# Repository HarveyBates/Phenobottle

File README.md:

---

### Description

An open-source Raspberry-Pi based photobioreactor for cultivating and assessing physiology (photosynthesis & productivity) in microscopic algae. The device can be used to cultivate both green algae and cyanobacteria while continuiously (and non-invasively) probing photosynthetic and growth phenotypes.

#### Publication

The device was published in [Algal Research in 2020](https://www.sciencedirect.com/science/article/abs/pii/S2211926420309735):

*The Phenobottle, an open-source photobioreactor platform for environmental simulation - Bates et al. 2020*

#### Future of The Phenobottle

The Phenobottle is currently being updated to version 0.2. This will feature several environmental controls that were not featured the original version (v0.1) of the device. Additonal environmental sensors will also feature in version 0.2 along with a graphical user interface (GUI). 

If you would like to learn more about the progress of this version please email: [harvey_bates@hotmail.com](harvey_bates@hotmail.com)

---

### [Live](https://youtu.be/7FyAfFrLizw) Preview

___

# Operating Manual

## Specifications

| Feature                                                      | Value / Description                                          |
| ------------------------------------------------------------ | ------------------------------------------------------------ |
| Growth light quality                                         | Red, green and blue (Adjustable). 8-bit individual adjustment for each channel. |
| Growth light intensity                                       | Up to 200 &mu;E (can be increased if needed).                |
| Mixing                                                       | Vertical mixing using magnetic stirrer (adjustable intensity) |
| Bubbling                                                     | Included bubbling motor (adjustable) or solenoid control for external supply of CO<sub>2</sub> |
| Main board                                                   | Raspberry Pi 3B+ (can accomidate the new 4 - 4B)             |
| Microcontroller                                              | Teensy 3.5/3.6 or Teensy 4.1 (3.6 Recommended)               |
| Actinic LED colors                                           | **Blue** 455 – 485 nm (466 nm), **Green** 517 – 555 nm (532 nm), **Orange** 583 – 600 nm (593 nm), **Red** 617 – 635 nm (626 nm). |
| Resolution of **optical density** and **chlorophyll fluorescence** measurments | 10 to 16-bit (adjustable)                                    |
| Sampling rate of fluorometer                                 | 8 &mu;s at 12-bits (can be overclocked)                      |
| Operating voltage                                            | 15 V 1.2 A (Barrel plug), 12 V 2 A (Barrel Plug) and a 5 V 2 A (MicroUSB) power supply |
| Data collection                                              | SQL Server and local .csv                                    |

## Downloading files from this repository

As the Phenobottle is being updated constantly, please download a released version of the device from the releases tab (located on the right hand side of the screen). This contains all the files needed to 3D-print and control Phenobottles as well as some information about the required materials and tools. 

If you wish to clone the main repository you may; however, as there are new versions of the Phenobottle in the works, the files may not work as planned.

## Python dependencies

A number of packages are included in the [Phenobottle_RaspberryPi.py](Phenobottle_RaspberryPi.py). Some of which are already installed on a Raspberry Pi and as such wont be discussed. Others need to be installed using the Raspberry Pi terminal before compiling, these include: 
### PyMySQL - For SQL connection
#### Terminal
```bash
pip3 install PyMySQL
```
#### Python
```python
import pymysql.cursors
```
This requires a Raspberry Pi to be configured as a dedicated SQL server. Information on how to do that can be found [here](https://pimylifeup.com/raspberry-pi-mysql/). It is recomended that you use a dedicated Raspberry Pi for the SQL server; however, you can use one of the Phenobottle's Raspberry Pi's as a server if you are limited.

### Adafruit_MotorHAT - For I2C communication with the [Adafruit-MotorHAT](https://www.adafruit.com/product/2348)
#### Terminal
```bash
git clone https://github.com/adafruit/Adafruit-Motor-HAT-Python-Library.git
cd Adafruit-Motor-HAT-Python-Library
python3 setup.py install
```
#### Python
```python
from Adafruit_MotorHAT import Adafruit_MotorHAT
```
Unfortunatly this package is depreciated; however, its still fine to use for the Phenobottle.

### Twilio - SMS messaging
#### Terminal
```bash
pip3 install twilio
```
#### Python
```python
from twilio.rest import Client
```
This package is not required if you do not want to recieve SMS updates. Twilio is a paid service that you must sign up for [here](https://www.twilio.com/). However, this is non-essential and the Phenobottle runs fine without this addition. This can be handy if you are away from The Phenobottle and need to know how the experiment is running. 

### pySerial - Serial (USB) communication with the microcontroller
#### Terminal
```bash
python3 -m pip install pyserial
```
#### Python
```python
import serial
```
Required for communication with the Teensy 3.6 microcontroller. Documentation on this package can be found [here](https://pyserial.readthedocs.io/en/latest/index.html). 

## Required setup in [Phenobottle_RaspberryPi.py](Phenobottle_RaspberryPi.py)
### Basic Setup
```python
PHENOBOTTLE_NUMBER = 3 # Arbitary number to differentiate between Phenobottles
INITIAL_OPTICAL_DENSITY = 888 # 12-bit value obtained by calibrating the optical density sensor
ARDUINO_FLUORESCENCE_REFERENCE = 3.3 # Teensy microntrollers have 2 analog reference values 1.1 and 3.3 
MIXING_SPEED = 32 # Mixing speed of the mixing motor (0 - 255)
BUBBLING_INTENSITY = 60 # Bubbling intensity of the bubbling motor (0 - 255)
LIGHT_INTENSITY = 220 # Overall light intensity of the grow lights (0 - 255) 
PERISTALTIC_SPEED = 160 # Speed of the peristaltic pump (0 - 255)
EXPERIMENT_START_TIME = "07:00:00" # Specify when the experiment should start 

ser = serial.Serial('/dev/ttyACM0', 115200) # Serial port and baud rate of Teensy 3.6 microcontroller
```
The `INITAL_OPTICAL_DENSITY` value is obtained by reading the raw value of optical density BEFORE adding microalgae to the flask. This can be acheived by writing "MeasureOpticalDensity" in the serial input of the Teensy 3.6 microcontroller (in the ArduinoIDE) or calling `Test.prelim_od()` in the python [file](Phenobottle_RaspberryPi.py). This is required to obtain a 100% transmission reading for which optical density measurments can be formulated from in the code. 

### SQL Setup
```python
connection = pymysql.connect(host='IP_ADDRESS', # IP address of Raspberry Pi SQL server
                             port=port_number, # Usually 3306
                             user='Username', # Username of phpmyadmin 
                             password='Password', # Password of phpmyadmin
                             db='Phenobottle No.%s' %PHENOBOTTLE_NUMBER, # Database name
                             charset='utf8mb4',
                             cursorclass=pymysql.cursors.DictCursor)
```
For a SQL server connection this command must be compiled. See [here](https://pypi.org/project/PyMySQL/) for some documentation related to PyMySQL. For the database name you can change this to whichever name you choose; however, here we have premaded databases in out SQL server named "Phenobottle No.1", "Phenobottle No.2" ..., so that the `PHENOBOTTLE_NUMBER` corresponds with the correct database. 

### Messaging Setup
```python
acc_sid = "Account SSID" # Accound SSID from Twilio
auth_token = "Account Token" # Accound token from Twilio
client = Client(acc_sid, auth_token)
from_number = "Twilio Phone Number" # Designated twilio phone number
to_number = "Mobile Phone Number" # Your phone number
```
As mentioned above, this part isn't really nessessary. However, information regarding the setup of SMS messaging can be found [here](https://www.twilio.com/).

## Experimental procedure
### Measurment Intervals
The Phenobottle is capable of measuring/controling environmental variables at described intervals. This is done through this set of commands:
```python
""" Here we can check if the current time in minutes is devisable by our required measuring interval in this case 10 minutes. This means every 10 minutes a routine (day or night) will be run."""
if datetime.datetime.now().minute % 10 == 0: 
    """ Here we can setup or morning (8:00) and night times (20:00)"""
    if Experiment.experiment_schedule(datetime.time(8, 00), datetime.time(20, 00)): 
        NOW = datetime.datetime.now()
        Experiment.day_routine() # Runs the day routine
    else:
        NOW = datetime.datetime.now() 
        Experiment.night_routine() # Runs the night routine
```
### Routines
The day and the night routine are idential except for the fact that during the night the LED grow lights are constantly switched OFF. 
```python
MotorsAndLights.light_on(None) # Turn on lights (daytime only) with desired color
MotorsAndLights.mixing_motor_on() # Mixing on at set speed
time.sleep(30) # Wait 30 seconds for mixing 

MotorsAndLights.mixing_motor_off() # Mixing off
MotorsAndLights.light_off() # Lights off to ensure no noise from PWM interferes with measurments
Sensors.measure_optical_density() # Measures optical density
Sensors.measure_fluorescence() # Measures fluorescence

MotorsAndLights.light_on(None) # Turn on lights (daytime only) with desired color
MotorsAndLights.peristaltic_motor_on() # Pump on to clear cuvette
Database.upload() # Upload to SQL server
Excel.upload() # Upload to local .csv file
time.sleep(20) # Wait for pump to clear cuvette 

MotorsAndLights.peristaltic_motor_off() # Stop pump
MotorsAndLights.bubbling_motor_on() # Bubble main culture flask on
MotorsAndLights.mixing_motor_on() # Mixing on to homogenate culture
time.sleep(30) # Wait 30 seconds for bubbling and mixing 

MotorsAndLights.bubbling_motor_off() # Bubbling off
MotorsAndLights.mixing_motor_off() # Mixing off
```
This procedure is completely customisable, i.e. methods can be swapped around and the length of certain processes such as the bubbling time can be increased easily. 

# [Teensy 3.6](https://www.pjrc.com/store/teensy36.html) Microcontroller 
Analog functions are carried out by a Teensy 3.6 microcontroller which is connected to the Rasberry Pi via a serial (USB) connection. These analog functions include the measurement of optical density (growth), temperture and chlorophyll fluorescence (photosynthesis). 

The Teensy microcontroller can be programed with the [Arduino IDE](https://www.arduino.cc/en/Main/Software) on the Raspberry Pi if the additional software provided by [PJRC](https://www.pjrc.com/) called [Teensyduino](https://www.pjrc.com/teensy/teensyduino.html) is installed. 

The Teensy [code](Phenobottle_Teensy.ino) is flashed to the Teensy board and doesn't need modifying as it acts as a slave to the Raspberry Pi. 

## Teensy Setup
```c++
void setup() {
  Serial.begin(115200); // Initalise serial communications at specific baud rate
  analogReadResolution(12); // Set the resolution of the microcontroller in bits
  set_reference_voltage(refVoltage); // Only applicable with a Teensy 3.6 (disable if using other microcontroller)
  ...
}
```
## Teensy Slave Setup
The Teensy is constantly checking if there is requests in its serial port from the Raspberry Pi. It does this via the main loop:
```c++
void loop(){
  if(Serial.available()){   
    command = Serial.readStringUntil('\n');
    if(command.equals("MeasureOpticalDensity") || command.equals("MOD")){
      measure_optical_density();
    }
    else if(command.equals("MeasureFluorescence") || command.equals("MF")){
      measure_fluorescence();
    }
    ...
}
```
For example, when a string containing ```"MeasureOpticalDensity"``` into the Teensy's serial port, the resulting function ```measure_optical_density()``` is carried out. This simple design makes it easy to add new requests from the Raspberry Pi [.py](Phenobottle_RaspberryPi.py) file and the Teensy [.ino](Phenobottle_Teensy.ino) file by adding a new `else if` statement to this loop. 

## Fluorescence Measurment
### Setup
The Teensy in its current configuration takes a one second measurement of chlorophyll fluorescence, this however, can be adjusted as described below. The first part is to create arrays of different sizes corresponding to the time between measurements of fluorescence. The one second measurement is comprised of over 2000 data points which are comprised of fast (microsecond timescales) and slow (millisecond timescales) measurments:
2. Micro - Comprised of microsecond measurments (~8 &mu;s between measurments) of a set amount
3. Milli - Comprised of millisecond measurements (~1 ms between measurements) of a set amount
```c++
// Setup arrays that hold fluorescence data
int microRead [1000];
int milliRead[1000];

// Setup arrays that hold timestamps that correspond to fluorescence values
float microTime[1000]; 
float milliTime[1000];
String command;

int microLength = 1000, milliLength = 1000; // Change these to match the size of the above arrays
```
### Read
The measurment procedure is as follows:
```c++
void measure_fluorescence() {
  set_reference_voltage(refVoltage); 
  digitalWrite(actinicPin, HIGH); // Turn on actinic LED
  long timer = micros(); // Start timer 
  ...
```
The measurment is carried out in two seperate parts (1) `microRead` and (2) `milliRead`. The `analogRead` values are stored in their respective arrays with corresponding timestamps in their own array.
```c++
  // Read microsecond fluorescence values and corresponding timestamps
  for (unsigned int i = 0; i < sizeof(microRead) / sizeof(int); i++) 
  {
    microRead[i] = analogRead(fluorescenceReadPin);
    microTime[i] = micros() - timer;
  }

  // Read millisecond fluorescence values and corresponding timestamps
  for (unsigned int i = 0; i < sizeof(milliRead) / sizeof(int); i++) 
  {
    milliRead[i] = analogRead(fluorescenceReadPin);
    milliTime[i] = micros() - timer;
    delay(1); // Delay ~ 1ms between aqusisitions
  }
  ...
```
Any processing (converting timestamps from `micros` to milliseconds) of the arrays after this measurment is carried out after the actinic LED is switched off. This speeds up the `analogRead` function as we only need to store array values while measuring. 

## Optical Density
Measurment of optical density is really simple. 
```c++
void measure_optical_density(){
  set_reference_voltage(refVoltage);
  digitalWrite(odEmitPin, HIGH); // Turn on emitting LED
  delay(500); // Slight delay to ensure emitting LED is stable
  int odMeasure = analogRead(odReadPin); // Read optical density
  Serial.println(odMeasure);
  digitalWrite(odEmitPin, LOW); // Turn off emitting LED
}
```

# Open-Source Licensing

The software in this work is licensed under GNU AFFERO GENERAL PUBLIC LICENSE
  Copyright (C) (2020)  (Harvey Bates)

  This program is free software: you can redistribute it and/or modify
  it under the terms of the GNU General Public License as published by
  the Free Software Foundation, either version 3 of the License, or
  (at your option) any later version.

  This program is distributed in the hope that it will be useful,
  but WITHOUT ANY WARRANTY; without even the implied warranty of
  MERCHANTABILITY or FITNESS FOR A PARTICULAR PURPOSE.  See the
  GNU General Public License for more details.

  You should have received a copy of the GNU General Public License
  along with this program.  If not, see <https://www.gnu.org/licenses/>

  For more information contact: harvey.bates@student.uts.edu.au

Hardware (3D Models, Electronic Schematics) in this work is licensed under a <a rel="license" href="http://creativecommons.org/licenses/by-sa/3.0/">Creative Commons Attribution-ShareAlike 3.0 Unported License</a>.

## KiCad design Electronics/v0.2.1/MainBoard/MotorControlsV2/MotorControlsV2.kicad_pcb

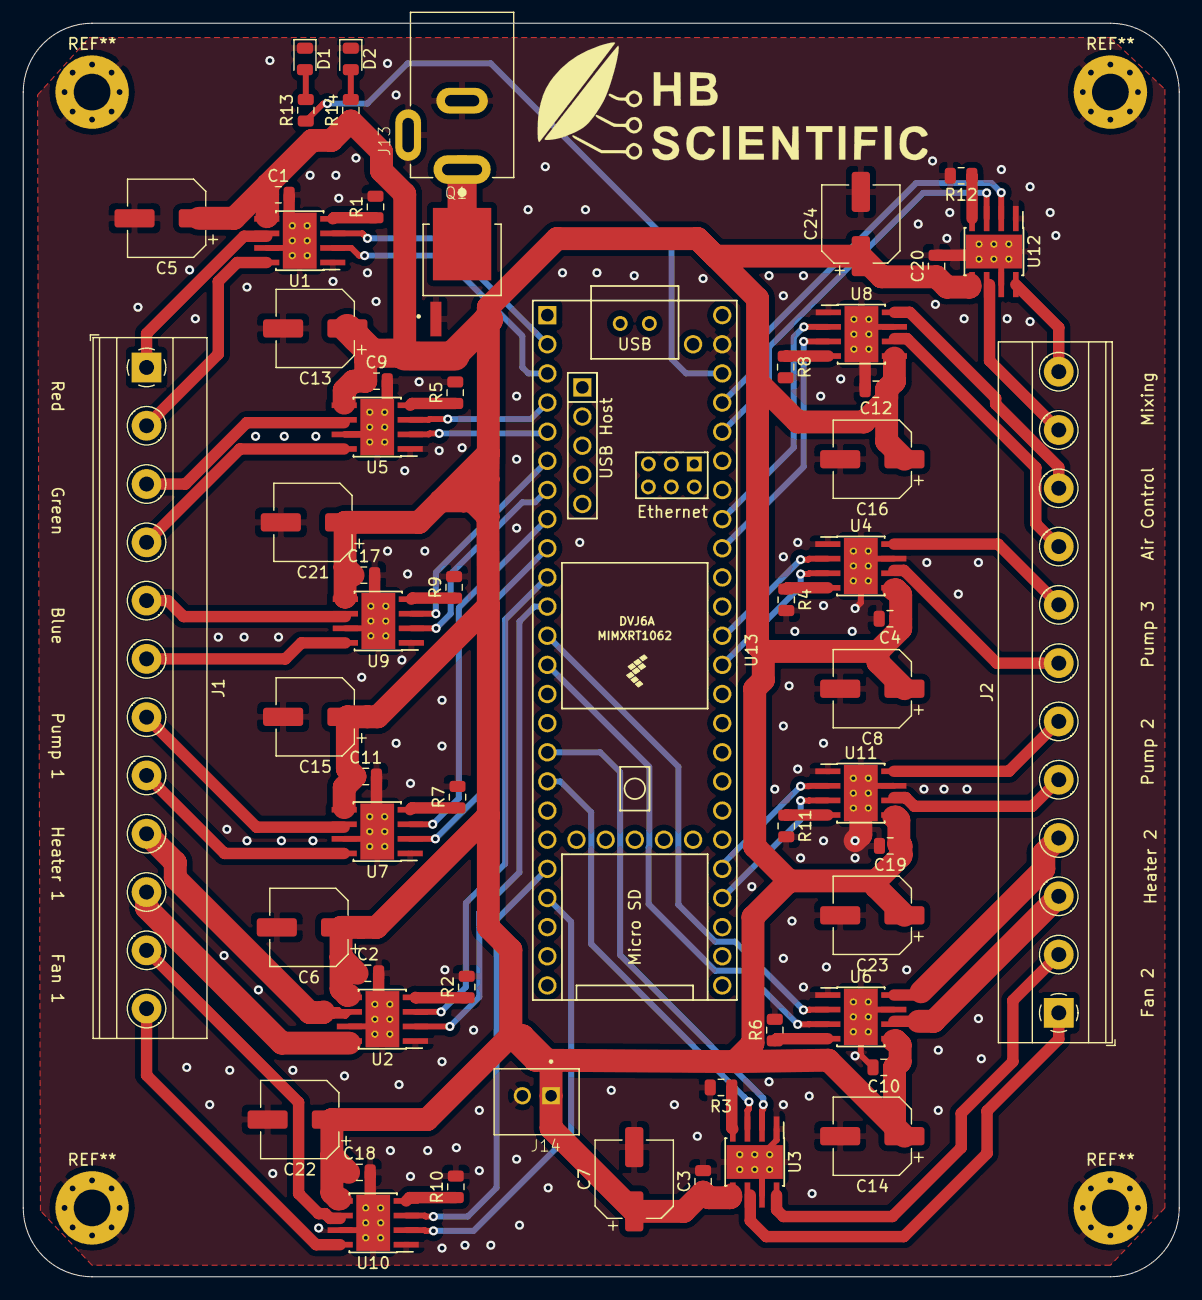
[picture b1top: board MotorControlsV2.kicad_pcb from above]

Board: 2 copper layers, 100.8 x 109.2 mm, 58 parts (0 on the bottom side), 66 nets.

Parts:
C1, C2, C3, C4, C9, C10, C11, C12, C17, C18, C19, C20: 0.1; C_0805_2012Metric
C5, C6, C7, C8, C13, C14, C15, C16, C21, C22, C23, C24: 47uF; CP_Elec_6.3x5.4
D1, D2: LED; LED_0805_2012Metric
J1, J2: Screw_Terminal_01x12; TerminalBlock_Phoenix_MKDS-1,5-12-5.08_1x12_P5.08mm_Horizon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
J13: PJ-002B; CUI_PJ-002B
J14: B2B-XH-A(LF)(SN); JST_B2B-XH-A(LF)(SN)
Q1: AOD417; DPAK228P994X240_3N
R1, R2, R3, R4, R5, R6, R7, R8, R9, R10, R11, R12: 30K; R_0805_2012Metric
R13: 320; R_0805_2012Metric
R14: 5K; R_0805_2012Metric
U1, U2, U3, U4, U5, U6, U7, U8, U9, U10, U11, U12: DRV8871DDA; Texas_HTSOP-8-1EP_3.9x4.9mm_P1.27mm_EP2.95x4.9mm_Mask2.4x3.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
U13: Teensy4.1; Teensy41

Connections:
+3V3: R13.1, U13.46
+12V: C1.1, C2.1, C3.1, C4.1, C5.1, C6.1, C7.1, C8.1, C9.1, C10.1, C11.1, C12.1, C13.1, C14.1, C15.1, C16.1, C17.1, C18.1, C19.1, C20.1, C21.1, C22.1, C23.1, C24.1, J14.1, Q1.3, R14.1, U1.5, U2.5, U3.5, U4.5, U5.5, U6.5, U7.5, U8.5, U9.5, U10.5, U11.5, U12.5
/A1: J2.9, U8.6
/A2: J2.10, U8.8
/B1: J1.5, U9.6
/B2: J1.6, U9.8
/F11: J1.11, U10.6
/F12: J1.12, U10.8
/F21: J2.1, U3.6
/F22: J2.2, U3.8
/G1: J1.3, U5.6
/G2: J1.4, U5.8
/H11: J1.9, U2.6
/H12: J1.10, U2.8
/H21: J2.3, U6.6
/H22: J2.4, U6.8
/M1: J2.11, U12.6
/M2: J2.12, U12.8
/P11: J1.7, U7.6
/P12: J1.8, U7.8
/P21: J2.5, U11.6
/P22: J2.6, U11.8
/P31: J2.7, U4.6
/P32: J2.8, U4.8
/PWM0: U1.3, U13.2
/PWM1: U1.2, U13.3
/PWM2: U5.3, U13.4
/PWM3: U5.2, U13.5
/PWM4: U9.3, U13.6
/PWM5: U9.2, U13.7
/PWM6: U7.3, U13.8
/PWM7: U7.2, U13.9
/PWM8: U2.3, U13.10
/PWM9: U2.2, U13.11
/PWM10: U6.2, U13.12
/PWM11: U6.3, U13.13
/PWM14: U4.3, U13.36
/PWM15: U4.2, U13.37
/PWM18: U8.3, U13.40
/PWM19: U8.2, U13.41
/PWM22: U12.3, U13.44
/PWM23: U12.2, U13.45
/PWM24: U3.2, U13.16
/PWM25: U3.3, U13.17
/PWM28: U10.3, U13.20
/PWM29: U10.2, U13.21
/PWM36: U11.3, U13.28
/PWM37: U11.2, U13.29
/R1: J1.1, U1.6
/R2: J1.2, U1.8
GND: C1.2, C2.2, C3.2, C4.2, C5.2, C6.2, C7.2, C8.2, C9.2, C10.2, C11.2, C12.2, C13.2, C14.2, C15.2, C16.2, C17.2, C18.2, C19.2, C20.2, C21.2, C22.2, C23.2, C24.2, D1.1, D2.1, J13.2, J13.3, J14.2, Q1.1, R1.2, R2.2, R3.2, R4.2, R5.2, R6.2, R7.2, R8.2, R9.2, R10.2, R11.2, R12.2, U1.1, U1.7, U1.9, U2.1, U2.7, U2.9, U3.1, U3.7, U3.9, U4.1, U4.7, U4.9, U5.1, U5.7, U5.9, U6.1, U6.7, U6.9, U7.1, U7.7, U7.9, U8.1, U8.7, U8.9, U9.1, U9.7, U9.9, U10.1, U10.7, U10.9, U11.1, U11.7, U11.9, U12.1, U12.7, U12.9, U13.47
unnamed: D1.2, R13.2
unnamed: D2.2, R14.2
unnamed: J13.1, Q1.4
unnamed: R1.1, U1.4
unnamed: R2.1, U2.4
unnamed: R3.1, U3.4
unnamed: R4.1, U4.4
unnamed: R5.1, U5.4
unnamed: R6.1, U6.4
unnamed: R7.1, U7.4
unnamed: R8.1, U8.4
unnamed: R9.1, U9.4
unnamed: R10.1, U10.4
unnamed: R11.1, U11.4
unnamed: R12.1, U12.4

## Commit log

2020-03-23 Create LICENSE
    Added License
2020-03-23 Update LICENSE
    Phenobottle Software License
2020-03-23 Software License
2020-03-23 Rename LICENSE to LICENSE (Software)
2020-03-24 Create LICENSE (Hardware)
2020-03-24 Update LICENSE (Hardware)
2020-03-24 Rename Phenobottle Raspberry Pi.py to Phenobottle_RaspberryPi.py
2020-03-30 Fixed Pin Indexing
2020-03-30 Added support for RGB Control and Dawn/Dusk mimic
2020-03-30 Added RGB Support
2020-09-05 Update Phenobottle Main Frame.step
    Added vent for Raspberry Pi, Teensy 3.6 PCB housing, routing for Mixing Motor
2020-10-20 RGB LED Functions
2020-10-20 fixed some alignment issues
2020-10-20 update released versions
2020-10-20 added raspberry pi information
2020-10-20 added Teensy information
2020-10-20 realignment
2020-10-20 Update for version 0.1.1
    Updated some of the documentation. Adjusted the Raspberry Pi controls of RGB LED's and added a new circuit for RGB control without extra outputs from the motor HAT.
2020-11-24 added comments and dynamic way of setting reference voltage
2020-11-25 rm ds.store
2020-11-25 rid of DS_Store
2020-11-29 began work on data visualiser
2020-11-29 update some plots
2020-11-29 added menubar functionallity
2020-12-06 added data visualizer
2020-12-06 update data visualizer readme
2020-12-22 updated main screen UI
2020-12-28 added teensy motorcontrols
2021-01-16 restructuring
2021-01-16 refactor for cmake
2021-01-16 renamed user inferface folder
2021-01-16 restructure user interface
2021-01-17 began work on web app
2021-01-17 started react app
2021-01-17 added plot placeholder
2021-01-18 added server-side boiler
2021-01-18 added dashboard/setup structure
2021-01-19 added multipage links
2021-01-20 backend boilerplate
2021-01-20 added CMAKE for cpr requests
2021-01-21 rm cmake files
2021-01-21 small amount of backend setup
2021-01-23 c++ server with js requests
2021-01-23 restrucutre into classes
2021-01-23 more work on websockets
2021-01-24 working websocket just needs propper decryptor
2021-01-24 working on decoding websocket comms
2021-01-24 decryption is hard
2021-01-25 decryption working with known pkg-length
2021-01-25 WebSocket working with pkt-size < 125
2021-01-25 added comments and removed unneeded libs
2021-01-26 removed unnecessary imports and adjusted cmake
2021-01-28 switching to .NET
2021-01-29 added json template
2021-01-29 working on extened msg frame decoding
2021-01-30 frame decoding <125 and 126
2021-01-30 working xor decryption for long and short frames
2021-01-30 added serial comms boilerplate
2021-01-31 added serial coms from js browser
2021-01-31 minor UI updates
2021-02-02 adding controls for reactor
2021-02-04 minor UI update
2021-02-06 connected postgreSQL db
2021-02-08 .net can access postgreSQL db and return data
2021-02-09 added number generation for connected devices
2021-02-11 added logo
2021-02-11 added constants.h
2021-02-11 restructured page routing
2021-02-12 let there be light
2021-02-13 added temperature cntrl and documentation
2021-02-13 prelim websocket to serial testing
2021-02-15 added support for unix devices
2021-02-15 restructure serial coms
2021-02-15 minor adjustment to cmake and port allocation
2021-02-21 update rpi support
2021-02-27 enabled client to serial port coms
2021-02-28 send and recieve serial msg from client
2021-03-01 adjusted for cli teensy control
2021-03-03 adjusting cmake for json formatting
2021-03-04 added json lib to cmake... what an effort
2021-03-07 led array with ir-leds
2021-03-09 led array IR-LED update:
2021-03-10 rm kicad cache
2021-03-10 added led array gerber
2021-03-12 Update LICENSE (Software)
2021-03-28 added basic code for tec controller
2021-04-24 fixed up serial port read functions
2021-04-25 fixed up json imports and added base json parser
2021-05-16 websockets only working over http
2021-06-07 react ui start
2021-06-08 added base docker image
2021-06-19 rearranged for mqtt
2021-06-20 started python control
2021-06-20 started api, ui and client
2021-06-25 restructure
2021-06-26 added base mqtt handling
2021-06-26 added base serial connections
2021-06-26 working on the site framework
2021-06-26 update gitignore
2021-06-27 updating ui
2021-06-27 updating ui some more
2021-06-28 learning react slowly
2021-06-29 i think i semi understand routing
2021-06-30 added UserContext
2021-07-06 working on device control
2021-07-07 updating login page
2021-07-17 working on logging and serial coms
2021-07-18 logging stack with confirmation
2021-07-18 minor changes
2021-09-18 update for video, heater and motor control
2021-11-22 12 V 3.2 - 3.5 A for the tec controller, heating fast but not cooling
2022-03-30 Bump minimist from 1.2.5 to 1.2.6 in /phenobottle-api
    Bumps [minimist](https://github.com/substack/minimist) from 1.2.5 to 1.2.6.
    - [Release notes](https://github.com/substack/minimist/releases)
    - [Commits](https://github.com/substack/minimist/compare/1.2.5...1.2.6)
    ---
    updated-dependencies:
    - dependency-name: minimist
2022-11-11 Bump minimatch from 3.0.4 to 3.1.2 in /phenobottle-api
    Bumps [minimatch](https://github.com/isaacs/minimatch) from 3.0.4 to 3.1.2.
    - [Release notes](https://github.com/isaacs/minimatch/releases)
    - [Commits](https://github.com/isaacs/minimatch/compare/v3.0.4...v3.1.2)
    ---
    updated-dependencies:
    - dependency-name: minimatch
2022-12-08 Bump qs and express in /phenobottle-api
    Bumps [qs](https://github.com/ljharb/qs) to 6.11.0 and updates ancestor dependency [express](https://github.com/expressjs/express). These dependencies need to be updated together.
    Updates `qs` from 6.7.0 to 6.11.0
    - [Release notes](https://github.com/ljharb/qs/releases)
    - [Changelog](https://github.com/ljharb/qs/blob/main/CHANGELOG.md)
    - [Commits](https://github.com/ljharb/qs/compare/v6.7.0...v6.11.0)
    Updates `express` from 4.17.1 to 4.18.2
2022-12-14 Bump express from 4.17.1 to 4.17.3 in /phenobottle-api
    Bumps [express](https://github.com/expressjs/express) from 4.17.1 to 4.17.3.
    - [Release notes](https://github.com/expressjs/express/releases)
    - [Changelog](https://github.com/expressjs/express/blob/master/History.md)
    - [Commits](https://github.com/expressjs/express/compare/4.17.1...4.17.3)
    ---
    updated-dependencies:
2023-02-03 Bump http-cache-semantics from 4.1.0 to 4.1.1 in /phenobottle-api
    Bumps [http-cache-semantics](https://github.com/kornelski/http-cache-semantics) from 4.1.0 to 4.1.1.
    - [Release notes](https://github.com/kornelski/http-cache-semantics/releases)
    - [Commits](https://github.com/kornelski/http-cache-semantics/compare/v4.1.0...v4.1.1)
    ---
    updated-dependencies:
    - dependency-name: http-cache-semantics
2023-02-11 Bump cacheable-request and nodemon in /phenobottle-api
    Removes [cacheable-request](https://github.com/jaredwray/cacheable-request). It's no longer used after updating ancestor dependency [nodemon](https://github.com/remy/nodemon). These dependencies need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
    Removes `cacheable-request`
    Updates `nodemon` from 2.0.7 to 2.0.20
    - [Release notes](https://github.com/remy/nodemon/releases)
    - [Commits](https://github.com/remy/nodemon/compare/v2.0.7...v2.0.20)
    ---
2023-03-06 Bump minimist from 1.2.5 to 1.2.8 in /phenobottle-api
    Bumps [minimist](https://github.com/minimistjs/minimist) from 1.2.5 to 1.2.8.
    - [Release notes](https://github.com/minimistjs/minimist/releases)
    - [Changelog](https://github.com/minimistjs/minimist/blob/main/CHANGELOG.md)
    - [Commits](https://github.com/minimistjs/minimist/compare/v1.2.5...v1.2.8)
    ---
    updated-dependencies:
2023-09-03 Update to start next round of testing
    Combining both Open-JIP electronics with Phenobottle electronics to
    consolidate circuit board. Next to add RPi attachment and drivers for
    peltier modules (optional).
2023-09-03 Added compute module and LED driver
    Need to change 5V regulator for higher current as compute module needs
    around 1 A with no peripherials (perhaps AP63205WU-7).
2023-09-04 updated 5V LDO with something that can power a RPi zero and other peripherals
2026-04-21 Bump python-dotenv from 0.17.1 to 1.2.2
    Bumps [python-dotenv](https://github.com/theskumar/python-dotenv) from 0.17.1 to 1.2.2.
    - [Release notes](https://github.com/theskumar/python-dotenv/releases)
    - [Changelog](https://github.com/theskumar/python-dotenv/blob/main/CHANGELOG.md)
    - [Commits](https://github.com/theskumar/python-dotenv/compare/v0.17.1...v1.2.2)
    ---
    updated-dependencies:

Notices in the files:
README.md:
CC BY-SA 3.0
Hardware (3D Models, Electronic Schematics) in this work is licensed under a Creative Commons Attribution-ShareAlike 3.0 Unported License.
